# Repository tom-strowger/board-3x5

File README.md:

# Tom's 3x5 board

## Overview
A keyboard built using ergogen etc.  36 keys wireless using the Seeed studio Xiao nRF52840 module.
This keyboard project heavily borrows from a few similar projects
- [triboard](https://github.com/tarneaux/triboard)
- [TOTEM](https://github.com/GEIGEIGEIST/TOTEM)

The main features of my board are:
- Split
- Wireless
- 36 keys: 5 columns x 3 rows + 3 thumb keys on each side
- Cherry MX switches with hotswap socket
- Uses the cheaper/smaller nordic mcu instead of nice nano
- The ergogen project generates two boards and cases (left and right)
  - The boards are not flippable as the battery charger pads on the mcu would not be reachable

## Images

## Guides
### Prerequisites
- `node` is setup to be run on the system
- For building cases: `npm install @jscad/csg` (this is a deprecated package so must be installed explicitly)

### How to generate the boards
`./build` (watches files and rebuilds when source changes/)

or

`./build once`

### How to generate the cases
`./build cases`

## TODO
- Increase the heat set insert radius as it is set with CA glue insted of being melted in (when printing with SLA resin)
- Add a printed part that slots over the switch and fits into the case allowing it to be easily comtrolled

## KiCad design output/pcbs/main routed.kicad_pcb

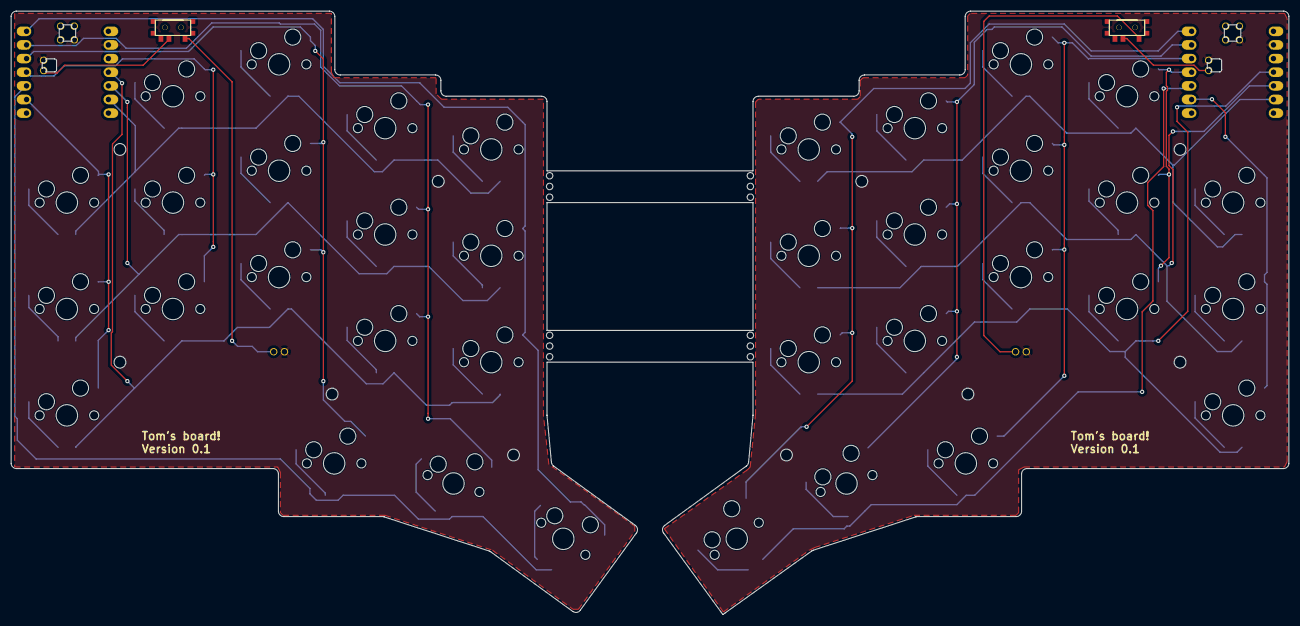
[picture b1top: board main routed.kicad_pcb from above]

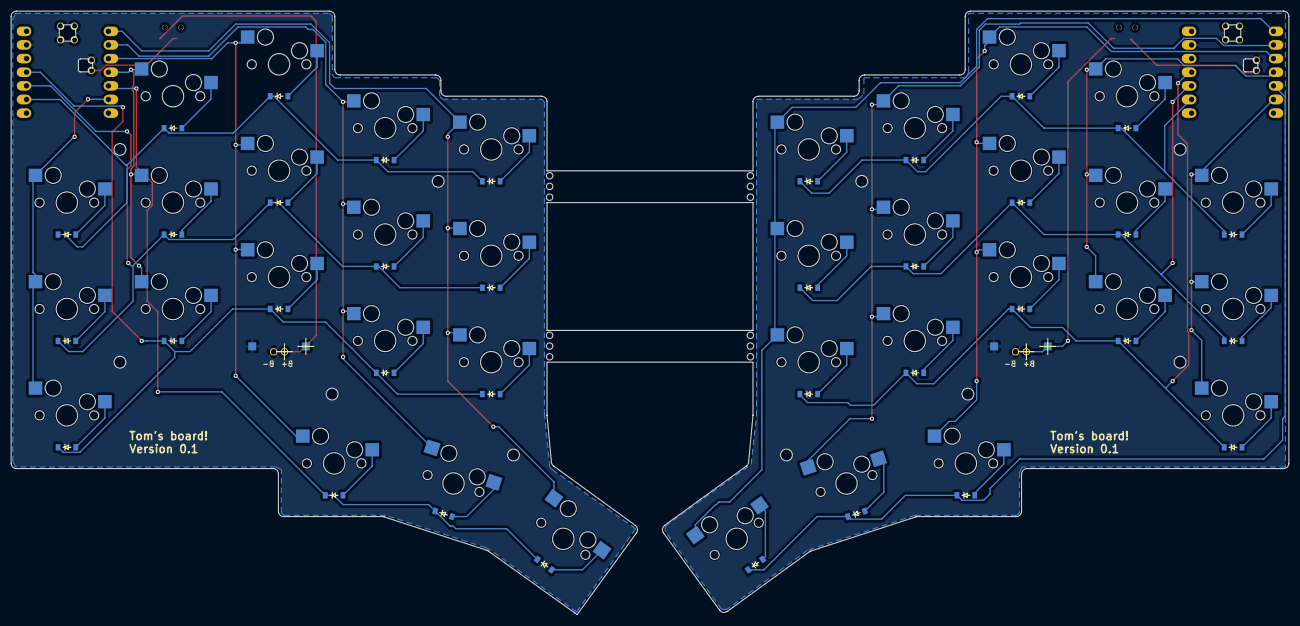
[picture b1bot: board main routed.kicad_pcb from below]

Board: 2 copper layers, 238.0 x 112.4 mm, 80 parts (36 on the bottom side), 60 nets.

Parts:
BATTPAD1, BATTPAD2, BATTPAD3, BATTPAD4: ComboDiode
D1, D2, D3, D4, D5, D6, D7, D8, D9, D10, D11, D12, D13, D14, D15, D16, D17, D18, D19, D20, D21, D22, D23, D24, D25, D26, D27, D28, D29, D30, D31, D32, D33, D34, D35, D36: ComboDiode
S1, S2, S3, S4, S5, S6, S7, S8, S9, S10, S11, S12, S13, S14, S15, S16, S17, S18, S19, S20, S21, S22, S23, S24, S25, S26, S27, S28, S29, S30, S31, S32, S33, S34, S35, S36: MX
T1, T2: SPDT_C128955
xiao-ble1, xiao-ble2: xiao-ble-thruhole; xiao-ble-smd-cutout

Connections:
L_BAT+: BATTPAD1.1, BATTPAD2.1, T1.1
L_GND: BATTPAD1.2, BATTPAD2.2, xiao-ble1.13, xiao-ble1.18, xiao-ble1.20
L_P0: S13.2, S14.2, S15.2, S18.2, xiao-ble1.1
L_P1: S10.2, S11.2, S12.2, S17.2, xiao-ble1.2
L_P2: S7.2, S8.2, S9.2, S16.2, xiao-ble1.3
L_P3: S4.2, S5.2, S6.2, xiao-ble1.4
L_P4: D16.1, D17.1, D18.1, xiao-ble1.5
L_P5: S1.2, S2.2, S3.2, xiao-ble1.6
L_P8: D3.1, D6.1, D9.1, D12.1, D15.1, xiao-ble1.9
L_P9: D2.1, D5.1, D8.1, D11.1, D14.1, xiao-ble1.10
L_P10: D1.1, D4.1, D7.1, D10.1, D13.1, xiao-ble1.11
L_RAW: T1.2, xiao-ble1.19
R_BAT+: BATTPAD3.1, BATTPAD4.1, T2.1
R_GND: BATTPAD3.2, BATTPAD4.2, xiao-ble2.13, xiao-ble2.18, xiao-ble2.20
R_P0: S31.2, S32.2, S33.2, S36.2, xiao-ble2.1
R_P1: S28.2, S29.2, S30.2, S35.2, xiao-ble2.2
R_P2: S25.2, S26.2, S27.2, S34.2, xiao-ble2.3
R_P3: S22.2, S23.2, S24.2, xiao-ble2.4
R_P4: D34.1, D35.1, D36.1, xiao-ble2.5
R_P5: S19.2, S20.2, S21.2, xiao-ble2.6
R_P8: D21.1, D24.1, D27.1, D30.1, D33.1, xiao-ble2.9
R_P9: D20.1, D23.1, D26.1, D29.1, D32.1, xiao-ble2.10
R_P10: D19.1, D22.1, D25.1, D28.1, D31.1, xiao-ble2.11
R_RAW: T2.2, xiao-ble2.19
home_thumb: D18.2, S18.1
index_bottom: D10.2, S10.1
index_home: D11.2, S11.1
index_top: D12.2, S12.1
inner_bottom: D13.2, S13.1
inner_home: D14.2, S14.1
inner_thumb: D16.2, S16.1
inner_top: D15.2, S15.1
middle_bottom: D7.2, S7.1
middle_home: D8.2, S8.1
middle_thumb: D17.2, S17.1
middle_top: D9.2, S9.1
mirror_home_thumb: D36.2, S36.1
mirror_index_bottom: D28.2, S28.1
mirror_index_home: D29.2, S29.1
mirror_index_top: D30.2, S30.1
mirror_inner_bottom: D31.2, S31.1
mirror_inner_home: D32.2, S32.1
mirror_inner_thumb: D34.2, S34.1
mirror_inner_top: D33.2, S33.1
mirror_middle_bottom: D25.2, S25.1
mirror_middle_home: D26.2, S26.1
mirror_middle_thumb: D35.2, S35.1
mirror_middle_top: D27.2, S27.1
mirror_pinky_bottom: D19.2, S19.1
mirror_pinky_home: D20.2, S20.1
mirror_pinky_top: D21.2, S21.1
mirror_ring_bottom: D22.2, S22.1
mirror_ring_home: D23.2, S23.1
mirror_ring_top: D24.2, S24.1
pinky_bottom: D1.2, S1.1
pinky_home: D2.2, S2.1
pinky_top: D3.2, S3.1
ring_bottom: D4.2, S4.1
ring_home: D5.2, S5.1
ring_top: D6.2, S6.1

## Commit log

2024-04-17 Initial board
    Lots borrow from other ergogen repos
    - https://github.com/tarneaux/triboard.git
    - https://github.com/Narkoleptika/josukey/
2024-04-21 Added breaks, battery thru hole, shift mcu up a touch to edge
2024-04-21 Fix diode layers
2024-04-23 Outputs from first version, routed
2024-04-23 Working on the case - WIP
2024-04-23 Working on bottom case
2024-04-25 The cases join cleaner, confirmed spacing of usb conn and switch
2024-04-27 Add heat set nuts, feet rings, usb reinforcement, centre switch gap
2024-04-27 Added battery holder underneath, increased het set size
2024-04-27 Case output, first version
2024-04-27 Split case, add battery holder to right
2024-04-28 Add walls to top, bottom sits on walls, increase usb tolerance
    This is being sent to manufacture
2024-04-29 Increase feet ring width to 1.5mm
    This is to meet manufacturing requirements
2024-04-29 Increase wall thickness so they are 1.5mm at the thinnest
2024-05-06 Adding firmware submodule
2024-05-08 Track jpg with git lfs
2024-05-08 Add images to readme
2024-05-08 Remove extra cases from root dir
2024-05-10 Stop tracking jpg as lfs
2024-05-10 Add images back without lfs
    This way they will appear in the readme
2025-04-21 Update project name
2025-04-21 Update zmk config
